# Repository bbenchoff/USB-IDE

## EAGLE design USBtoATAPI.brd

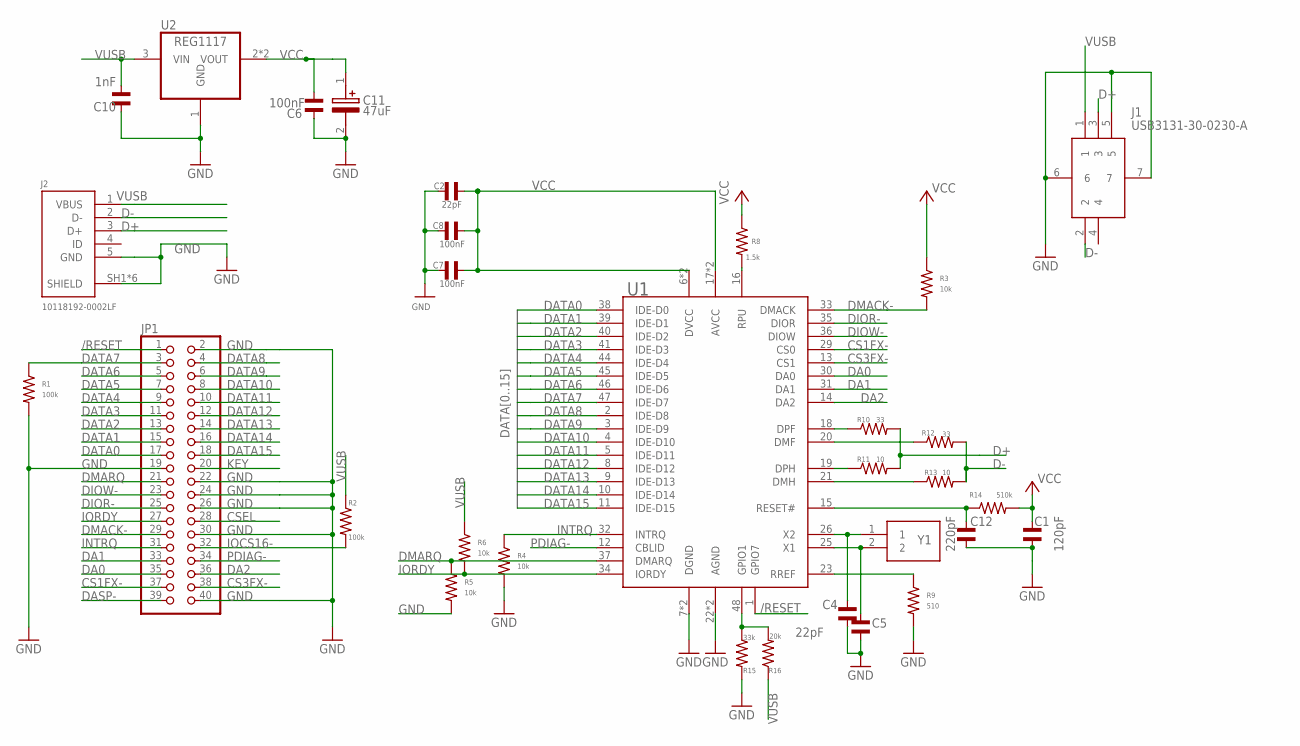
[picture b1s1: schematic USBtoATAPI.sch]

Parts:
C1: 120pF; C0805
C2, C4, C5: 22pF; C0805
C6, C7, C8: 100nF; C0805
C10: 1nF; C0805
C11: 47uF; CAPAE430X550N
C12: 220pF; C0805
J1: USB3131-30-0230-A; USB3131300230A
J2: 10118192-0002LF
JP1: PINHD-2X20; 2X20
R1, R2: 100k; R0805
R3, R4, R5, R6: 10k; R0805
R8: 1.5k; R0805
R9: 510; R0805
R10, R12: 33; R0805
R11, R13: 10; R0805
R14: 510k; R0805
R15: 33k; R0805
R16: 20k; R0805
U1: GL811E; LQFP-48
U2: REG1117; SOT223
Y1: 445C33C12M00000

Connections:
/RESET: JP1.1, U1.1 (GPIO7)
CS1FX-: JP1.37, U1.29 (CS0)
CS3FX-: JP1.38, U1.13 (CS1)
CSEL: JP1.28
D+: J1.3, J2.3 (D+), R10.P$2, R11.P$2
D-: J1.2, J2.2 (D-), R12.P$2, R13.P$2
DA0: JP1.35, U1.30 (DA0)
DA1: JP1.33, U1.31 (DA1)
DA2: JP1.36, U1.14 (DA2)
DASP-: JP1.39
DATA0: JP1.17, U1.38 (IDE-D0)
DATA1: JP1.15, U1.39 (IDE-D1)
DATA2: JP1.13, U1.40 (IDE-D2)
DATA3: JP1.11, U1.41 (IDE-D3)
DATA4: JP1.9, U1.44 (IDE-D4)
DATA5: JP1.7, U1.45 (IDE-D5)
DATA6: JP1.5, U1.46 (IDE-D6)
DATA7: JP1.3, R1.P$1, U1.47 (IDE-D7)
DATA8: JP1.4, U1.2 (IDE-D8)
DATA9: JP1.6, U1.3 (IDE-D9)
DATA10: JP1.8, U1.4 (IDE-D10)
DATA11: JP1.10, U1.5 (IDE-D11)
DATA12: JP1.12, U1.8 (IDE-D12)
DATA13: JP1.14, U1.9 (IDE-D13)
DATA14: JP1.16, U1.10 (IDE-D14)
DATA15: JP1.18, U1.11 (IDE-D15)
DIOR-: JP1.25, U1.35 (DIOR)
DIOW-: JP1.23, U1.36 (DIOW)
DMACK-: JP1.29, R3.P$2, U1.33 (DMACK)
DMARQ: JP1.21, R5.P$1, U1.37 (DMARQ)
GND: C1.P$1, C2.P$1, C4.P$2, C5.P$1, C6.P$1, C7.P$2, C8.P$2, C10.P$1, C11.2 (-), C12.P$1, J1.5, J1.6, J1.7, J2.5 (GND), J2.SH1 (SHIELD), J2.SH2 (SHIELD), J2.SH3 (SHIELD), J2.SH4 (SHIELD), J2.SH5 (SHIELD), J2.SH6 (SHIELD), JP1.2, JP1.19, JP1.22, JP1.24, JP1.26, JP1.30, JP1.40, R1.P$2, R4.P$2, R5.P$2, R9.P$2, R15.P$2, U1.7 (DGND), U1.22 (AGND), U1.27 (AGND), U1.42 (DGND), U2.1 (GND)
INTRQ: JP1.31, R4.P$1, U1.32 (INTRQ)
IOCS16-: JP1.32, R2.P$2
IORDY: JP1.27, R6.P$2, U1.34 (IORDY)
KEY: JP1.20
unnamed: C4.P$1, U1.26 (X2), Y1.1
unnamed: C5.P$2, U1.25 (X1), Y1.2
unnamed: R10.P$1, U1.18 (DPF)
unnamed: R11.P$1, U1.19 (DPH)
unnamed: R13.P$1, U1.21 (DMH)
unnamed: R12.P$1, U1.20 (DMF)
unnamed: R8.P$2, U1.16 (RPU)
unnamed: C12.P$2, R14.P$1, U1.15 (RESET#)
unnamed: R15.P$1, R16.P$2, U1.48 (GPIO1)
unnamed: R9.P$1, U1.23 (RREF)
PDIAG-: JP1.34, U1.12 (CBLID)
VCC: C1.P$2, C2.P$2, C6.P$2, C7.P$1, C8.P$1, C11.1 (+), R3.P$1, R8.P$1, R14.P$2, U1.6 (DVCC), U1.17 (AVCC), U1.24 (AVCC), U1.43 (DVCC), U2.2 (VOUT), U2.4 (VOUT)
VUSB: C10.P$2, J1.1, J2.1 (VBUS), R2.P$1, R6.P$1, R16.P$1, U2.3 (VIN)

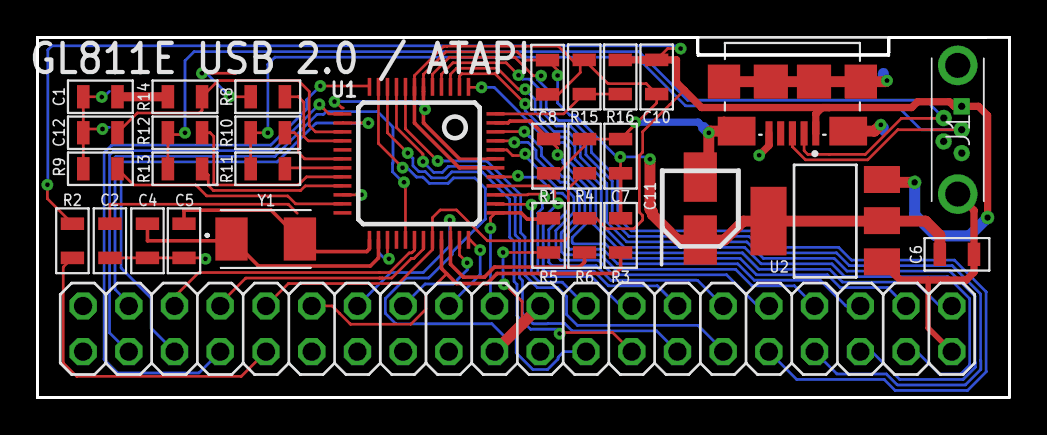
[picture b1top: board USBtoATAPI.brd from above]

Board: 2 copper layers, 54.0 x 20.0 mm, 31 parts (0 on the bottom side), 45 nets.

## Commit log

2021-08-30 Added files

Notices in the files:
parts and their libraries:
SparkFun-Aesthetics: Licensing: Creative Commons ShareAlike 4.0 International - https://creativecommons.org/licenses/by-sa/4.0
